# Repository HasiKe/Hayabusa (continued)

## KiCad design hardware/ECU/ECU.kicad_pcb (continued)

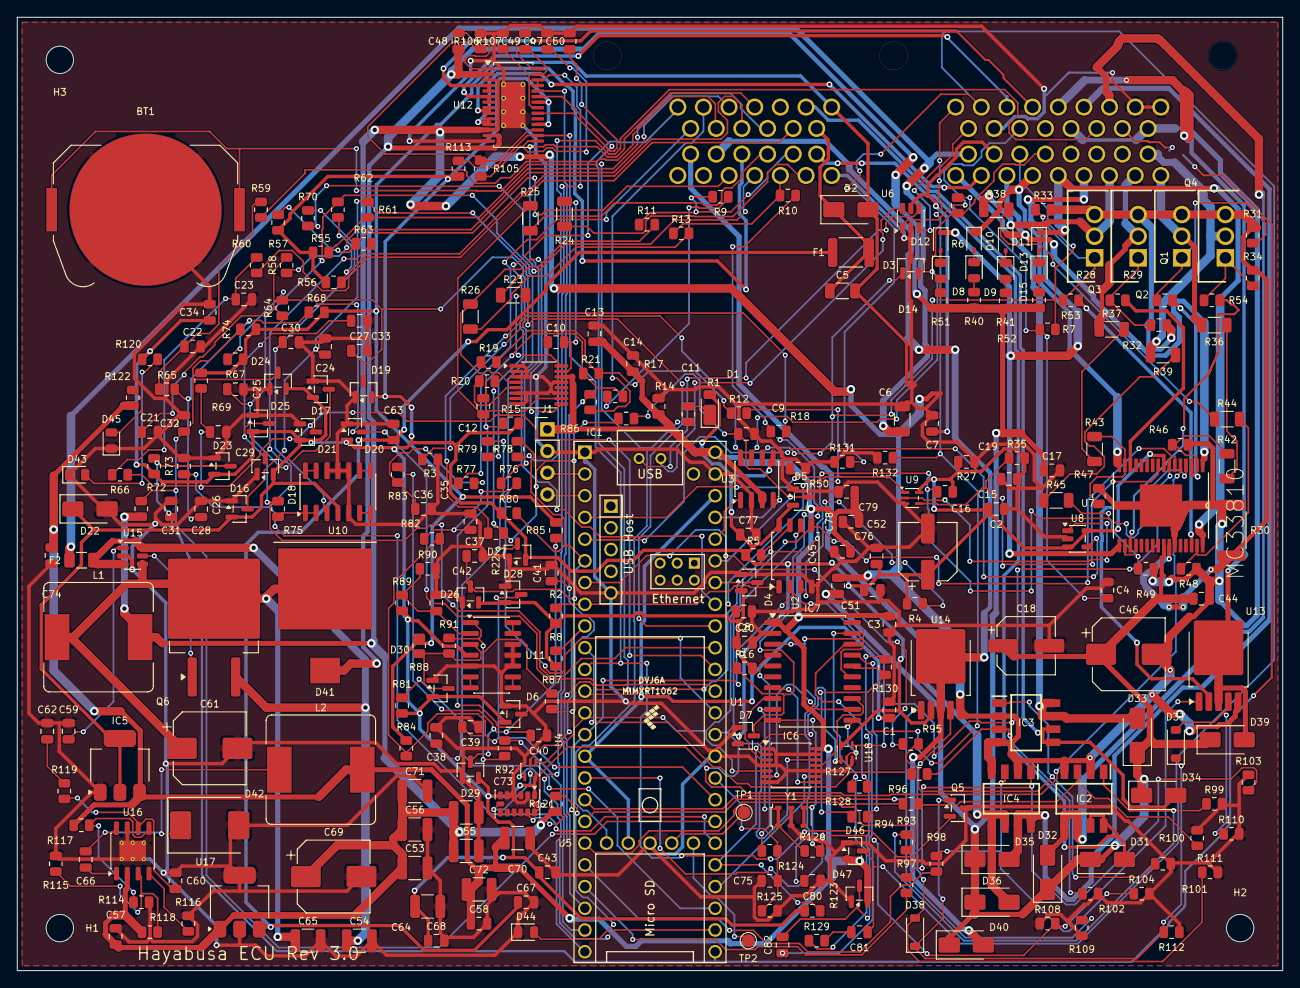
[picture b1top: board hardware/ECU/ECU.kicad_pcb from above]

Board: 2 copper layers, 148.0 x 111.5 mm, 307 parts (1 on the bottom side), 211 nets.

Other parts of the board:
H1, H2, H3: M3; MountingHole_3.2mm_M3

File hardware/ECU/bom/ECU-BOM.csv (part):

Reference,Qty,Value,Footprint,MPN,Manufacturer,DigiKey,DK_Stock,Mouser,MO_Stock,Chosen_Distributor,Datasheet,Validated,DNP,Notes
BT1,1,ML2032,BatteryHolder_Keystone_3034_1x20mm,3034,Keystone Electronics,36-3034-ND,,,,DigiKey,https://www.digikey.de/de/products/result?keywords=36-3034-ND,,,SMD-Halter 20 mm (Keystone 3034); Zelle ML2032 separat: Jauch ML2032 / DK 1908-ML2032-ND. Keine CR2032 (nicht ladbar)!
"C1,C38,C41,C43,C35,C42,C36,C37,C68,C74,C67,C21,C25,C22,C31,C32,C30,C34,C23,C24,C77,C7",22,100nF,0805,CC0805KRX7R9BB104,Yageo,311-1140-1-ND,,,,DigiKey,https://www.digikey.de/de/products/result?keywords=311-1140-1-ND,,,
C4,1,4.7nF,0805,CC0805KRX7R9BB472,Yageo,311-1133-1-ND,,,,DigiKey,https://www.digikey.de/de/products/result?keywords=311-1133-1-ND,,,
C5,1,10uF,1206,GRM31CR71E106KA12L,Murata,490-6518-1-ND,,,,DigiKey,https://www.digikey.de/de/products/result?keywords=490-6518-1-ND,,,
C6,1,100nF 100V,1206,C1206C104K1RACTU,KEMET,399-C1206C104K1RACTUCT-ND,,,,DigiKey,https://www.digikey.de/de/products/result?keywords=399-C1206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,,,
"C8,C9",2,470pF,0805,CC0805KRX7R9BB471,Yageo,311-1124-1-ND,,,,DigiKey,https://www.digikey.de/de/products/result?keywords=311-1124-1-ND,,,
"C11,C75",2,0.01uF,0805,CC0805KRX7R9BB103,Yageo,311-1136-1-ND,,,,DigiKey,https://www.digikey.de/de/products/result?keywords=311-1136-1-ND,,,
"C12,C10,C26",3,1nF,0805,C0805C102J5HACAUTO,Kemet,399-16591-1-ND,,,,DigiKey,https://www.digikey.de/de/products/result?keywords=399-16591-1-ND,,,
"C13,C3,C2,C15,C17",5,0.1uF,0805,CC0805KRX7R9BB104,Yageo,311-1140-1-ND,,,,DigiKey,https://www.digikey.de/de/products/result?keywords=311-1140-1-ND,,,
C14,1,1uF,0805,CC0805KKX7R7BB105,Yageo,311-1365-1-ND,,,,DigiKey,https://www.digikey.de/de/products/result?keywords=311-1365-1-ND,,,
"C18,C16",2,33uF,CP_Elec_6.3x7.7,EEE-1HA330XP,Panasonic,PCE3925CT-ND,,,,DigiKey,https://www.digikey.de/de/products/result?keywords=PCE3925CT-ND,,,
"C20,C19,C51,C52",4,100n,0805,CC0805KRX7R9BB104,Yageo,311-1140-1-ND,,,,DigiKey,https://www.digikey.de/de/products/result?keywords=311-1140-1-ND,,,
"C40,C39,C28,C29,C27,C33",6,10nF,0805,CC0805KRX7R9BB103,Yageo,311-1136-1-ND,,,,DigiKey,https://www.digikey.de/de/products/result?keywords=311-1136-1-ND,,,
"C45,C44",2,10n,0805,CC0805KRX7R9BB103,Yageo,311-1136-1-ND,,,,DigiKey,https://www.digikey.de/de/products/result?keywords=311-1136-1-ND,,,
C46,1,100u/50V,CP_Elec_8x10,EEE-FK1H101GP,Panasonic,PCE4323CT-ND,,,,DigiKey,https://www.digikey.de/de/products/result?keywords=PCE4323CT-ND,,,
C47,1,1u,0805,CC0805KKX7R7BB105,Yageo,311-1365-1-ND,,,,DigiKey,https://www.digikey.de/de/products/result?keywords=311-1365-1-ND,,,
C48,1,220n,0805,CC0805KKX7R9BB224,Yageo,311-1887-1-ND,,,,DigiKey,https://www.digikey.de/de/products/result?keywords=311-1887-1-ND,,,
C49,1,22n,0805,CC0805KRX7R9BB223,Yageo,311-1138-1-ND,,,,DigiKey,https://www.digikey.de/de/products/result?keywords=311-1138-1-ND,,,
C50,1,1n,0805,C0805C102J5HACAUTO,KEMET,399-16591-1-ND,,,,DigiKey,https://www.digikey.de/de/products/result?keywords=399-16591-1-ND,,,
"C53,C73,C54,C65",4,100nF/100V,1210,C1210C104K1RACTU,KEMET,399-C1210C104K1RACTUCT-ND,,,,DigiKey,https://www.digikey.de/de/products/result?keywords=399-C1210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,,,
"C56,C55",2,4.7uF/100V,1210,C3225X7S2A475K200AB,TDK,445-6042-1-ND,,,,DigiKey,https://www.digikey.de/de/products/result?keywords=445-6042-1-ND,,,
C57,1,1uF/50V,0805,CC0805KKX7R9BB105,Yageo,311-1886-1-ND,,,,DigiKey,https://www.digikey.de/de/products/result?keywords=311-1886-1-ND,,,
"C58,C63",2,10uF/10V,0805,CL21A106KPFNNNE,Samsung Electro-Mechanics,1276-1052-1-ND,,,,DigiKey,https://www.digikey.de/de/products/result?keywords=1276-1052-1-ND,,,
C60,1,39pF,0805,CC0805JRNPO9BN390,Yageo,311-1106-1-ND,,,,DigiKey,https://www.digikey.de/de/products/result?keywords=311-1106-1-ND,,,
"C61,C69",2,100uF/50V,CP_Elec_8x10,EEE-FK1H101GP,Panasonic,PCE4323CT-ND,,,,DigiKey,https://www.digikey.de/de/products/result?keywords=PCE4323CT-ND,,,
C62,1,6800pF,0805,CC0805KRX7R9BB682,Yageo,311-1135-1-ND,,,,DigiKey,https://www.digikey.de/de/products/result?keywords=311-1135-1-ND,,,
C64,1,22uF/10V,1210,GRM32ER71A226KE20L,Murata,490-1876-1-ND,,,,DigiKey,https://www.digikey.de/de/products/result?keywords=490-1876-1-ND,,,
"C66,C59",2,100nF/25V,0805,CC0805KRX7R9BB104,Yageo,311-1140-1-ND,,,,DigiKey,https://www.digikey.de/de/products/result?keywords=311-1140-1-ND,,,
C71,1,10uF/50V X7R,1210,C3225X7R1H106K250AC,TDK,445-C3225X7R1H106K250ACCT-ND,,,,DigiKey,https://www.digikey.de/de/products/result?keywords=445-C3225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,,,
"C72,C70",2,47uF/10V X7R,1210,CL32A476KOJNNNE,Samsung Electro-Mechanics,1276-3376-1-ND,,,,DigiKey,https://www.digikey.de/de/products/result?keywords=1276-3376-1-ND,,,
"C78,C80,C76",3,CC0805KRX7R9BB104,0805,CC0805KRX7R9BB104,Yageo,311-1140-1-ND,,603-CC805KRX7R9BB104,,DigiKey,https://www.yageo.com/upload/media/product/productsearch/dat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,,,
C79,1,CC0805KKX7R7BB475,0805,CC0805KKX7R7BB475,Yageo,311-1883-1-ND,,603-CC805KKX7R7BB475,,DigiKey,https://www.digikey.de/de/products/result?keywords=311-1883-1-ND,,,
"C82,C81",2,CC0805JRX7R9BB332,0805,CC0805JRX7R9BB332,Yageo,311-4277-1-ND,,,,DigiKey,https://yageogroup.com/content/datasheet/asset/file/UPY-GPHC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,,,
D1,1,D_Schottky,PowerDI-123,DFLS240-7,Diodes Incorporated,DFLS240-7DICT-ND,,,,DigiKey,https://www.digikey.de/de/products/result?keywords=DFLS240-7DICT-ND,,,
D2,1,SMAJ5.0A,SMA,SMAJ5.0A,Littelfuse,SMAJ5.0ALFCT-ND,,,,DigiKey,https://www.digikey.de/de/products/result?keywords=SMAJ5.0ALFCT-ND,,,
D3,1,NUP2105L,SOT-23,NUP2105LT1G,onsemi,NUP2105LT1GOSCT-ND,,,,DigiKey,https://www.digikey.de/de/products/result?keywords=NUP2105LT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,,,
"D11,D12,D10,D13",4,D,SOD-323,1N4448WX-TP,MCC,1N4448WXTPMSCT-ND,,,,DigiKey,https://www.digikey.de/de/products/result?keywords=1N4448WXT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,,,
"D15,D8,D14,D9",4,LED,0805,LTST-C170KRKT,Lite-On,160-1415-1-ND,,,,DigiKey,https://www.digikey.de/de/products/result?keywords=160-1415-1-ND,,,
D22,1,3V6 1W (SMA),SMA,1SMA5914BT3G,onsemi,1SMA5914BT3GOSCT-ND,,,,DigiKey,https://www.digikey.de/de/products/result?keywords=1SMA5914B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,,,
"D30,D27,D26,D28,D29,D7,D4,D5,D6,D20,D19,D25,D24,D23,D17,D16,D18,D21,D46,D47",20,BAV199,SOT-23,BAV199LT1G,onsemi,BAV199LT1GOSCT-ND,,,,DigiKey,https://www.digikey.de/de/products/result?keywords=BAV199LT1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,,,
"D31,D35,D40,D34,D36,D32,D33,D39",8,SS34,SMA,B340A-13-F,Diodes Incorporated,B340A-FDICT-ND,,,,DigiKey,https://www.digikey.de/de/products/result?keywords=B340A-FDICT-ND,,,Ersatz fuer SS34: 3A/40V Schottky in SMA (SS34 meist SMC)
"D38,D37",2,1N4148W,SOD-123,1N4148W-7-F,Diodes Incorporated,1N4148W-FDICT-ND,,,,DigiKey,https://www.digikey.de/de/products/result?keywords=1N4148W-FDICT-ND,,,
D41,1,SM8S24A,DO-218AB,SM8S24A,SMC Diode Solutions,1655-SM8S24ACT-ND,,,,DigiKey,https://www.digikey.de/de/products/result?keywords=1655-SM8S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,,,
D42,1,B560C,SMC,B560C-13-F,Diodes Incorporated,B560C-FDICT-ND,,,,DigiKey,https://www.digikey.de/de/products/result?keywords=B560C-FDICT-ND,,,
"D43,D44,D45",3,LED grn,0805,LTST-C170GKT,Lite-On,160-1179-1-ND,,,,DigiKey,https://www.digikey.de/de/products/result?keywords=160-1179-1-ND,,,
F1,1,150mA,1812,1812L014DR,Littelfuse,F3353CT-ND,,,,DigiKey,https://www.digikey.de/de/products/result?keywords=F3353CT-ND,,,"PTC 140mA hold (naechster Standardwert zu 150mA), 60V"
F2,1,3A / 63V,1206,0483003.DR,Littelfuse,18-0483003.DRCT-ND,,,,DigiKey,https://www.digikey.de/de/products/result?keywords=18-048300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,,,3A/65V flink 1206 (63V-Anforderung: 437er-Serie schafft nur 35V)
IC1,1,MAX9926UAEE_V+,QSOP-16_3.9x4.9mm_P0.635mm,MAX9926UAEE/V+,Analog Devices,MAX9926UAEE/V+-ND,,700-MAX9926UAEE/V+,,DigiKey,https://componentsearchengine.com/Datasheets/1/MAX9926UAEE_V+.pdf,,,
"IC3,IC4,IC2",3,ZXMS6006DT8,SOT153P700X170-8N,ZXMS6006DT8TA,Diodes Incorporated,ZXMS6006DT8TADICT-ND,,,,DigiKey,https://www.digikey.de/de/products/result?keywords=ZXMS6006D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,,,Last Time Buy 06.01.2027 - Bedarf sichern
IC5,1,LD1117S33,SOT-223-3_TabPin2,LD1117S33CTR,STMicroelectronics,497-1241-1-ND,,,,DigiKey,https://www.digikey.de/de/products/result?keywords=497-1241-1-ND,,,
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
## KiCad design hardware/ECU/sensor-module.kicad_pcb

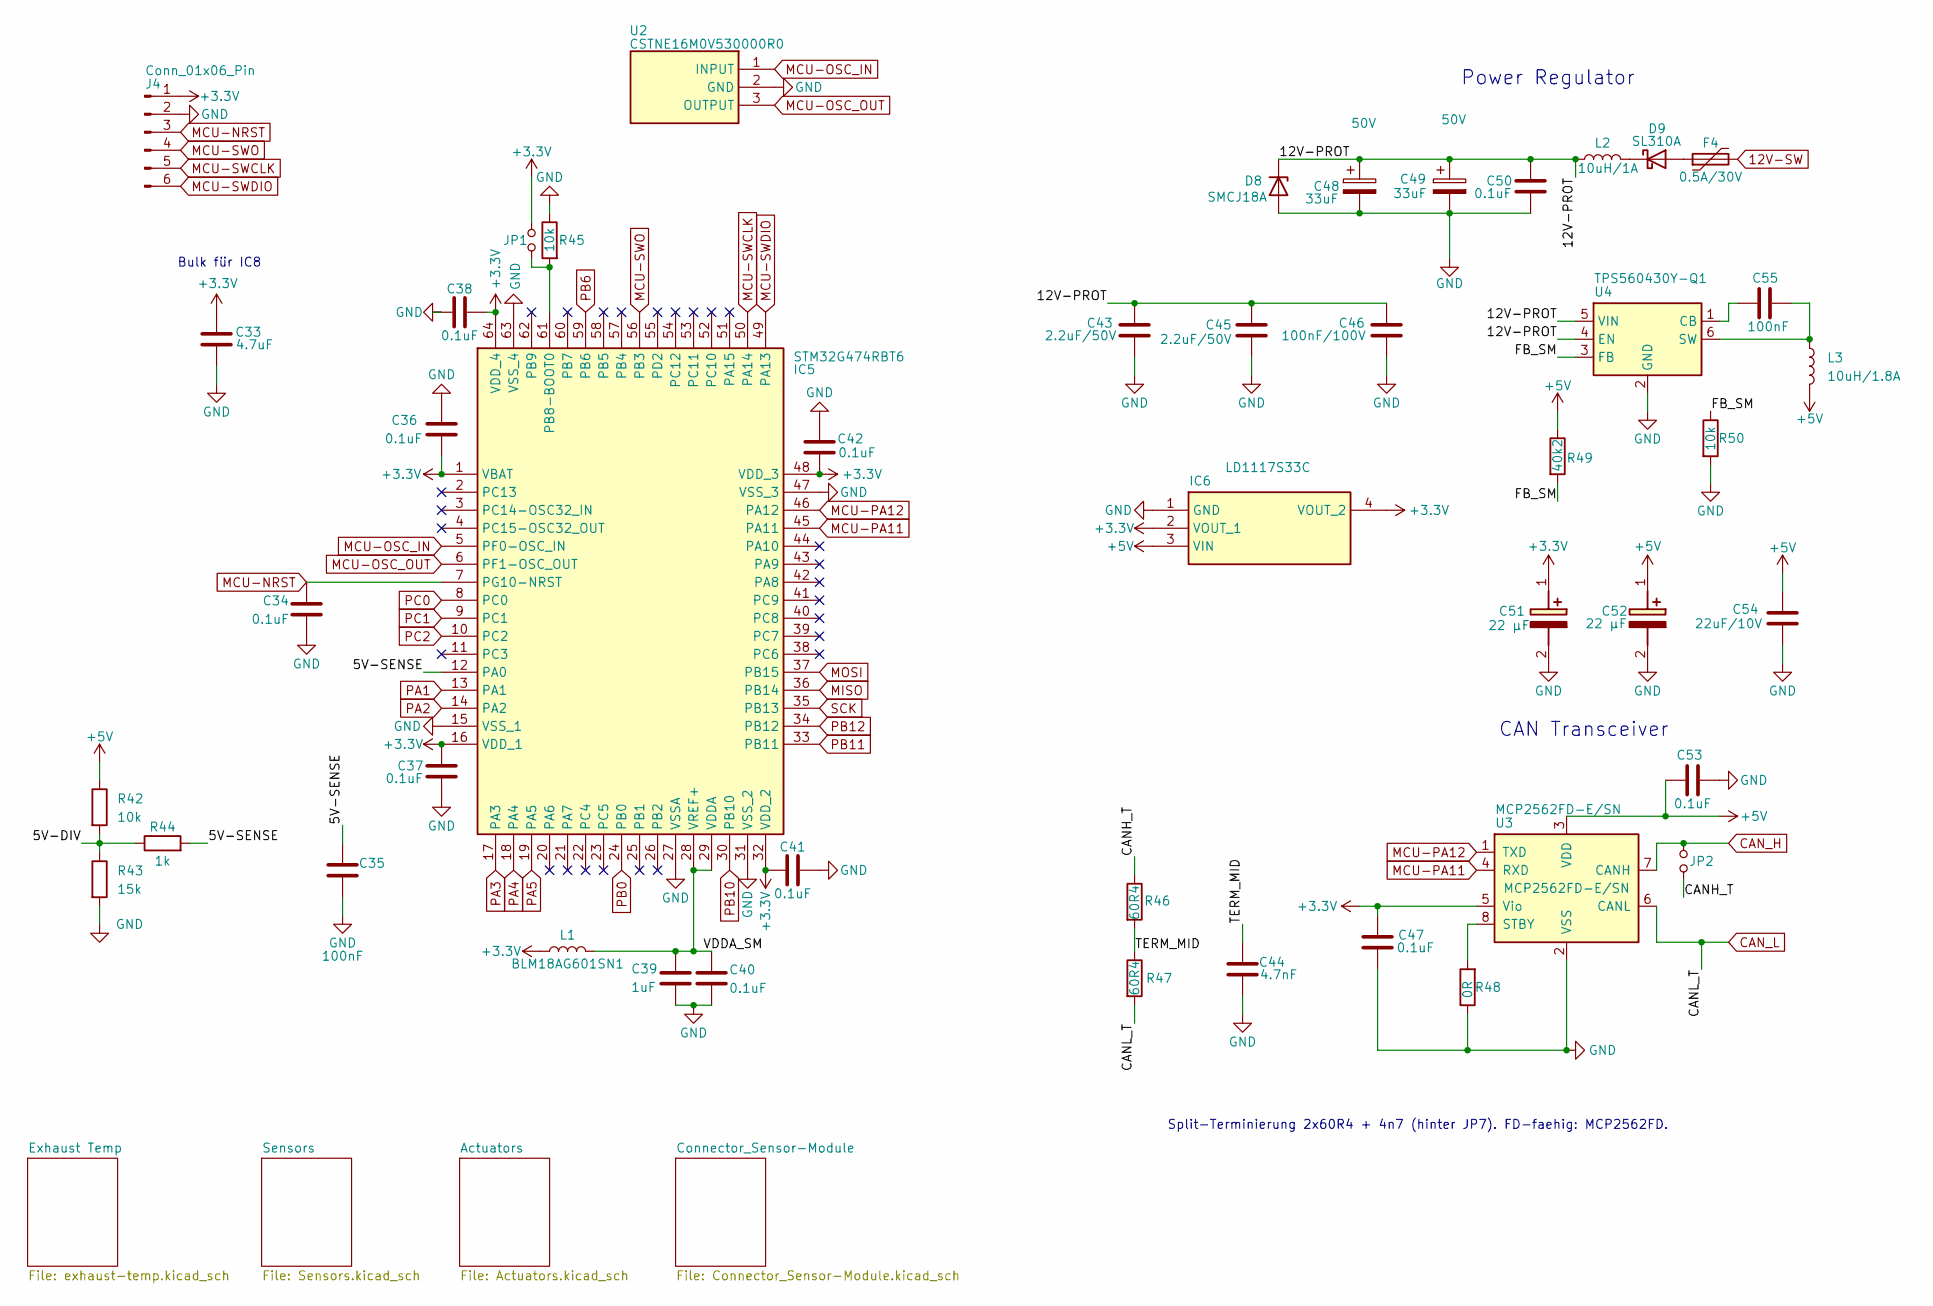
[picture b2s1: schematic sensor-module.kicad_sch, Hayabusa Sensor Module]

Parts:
C33: 4.7uF; C_0805_2012Metric; Manufacturer_Part_Number CC0805KKX7R7BB475; Digikey Part Number 311-1883-1-ND
C34, C36, C37, C38, C40, C41, C42, C47, C50, C53: 0.1uF; C_0805_2012Metric; Manufacturer_Part_Number CC0805KRX7R9BB104; Digikey Part Number 311-1140-1-ND
C35, C55: 100nF; C_0805_2012Metric; Manufacturer_Part_Number CC0805KRX7R9BB104; Digikey Part Number 311-1140-1-ND
C39: 1uF; C_0805_2012Metric; Manufacturer_Part_Number CC0805KKX7R7BB105; Digikey Part Number 311-1365-1-ND
C43, C45: 2.2uF/50V; C_1210_3225Metric; Manufacturer_Part_Number C3225X7R1H225K250AB; Digikey Part Number 445-1431-1-ND
C44: 4.7nF; C_0805_2012Metric; Manufacturer_Part_Number CC0805KRX7R9BB472; Digikey Part Number 311-1133-1-ND
C46: 100nF/100V; C_0805_2012Metric; Manufacturer_Part_Number C0805C104K1RACTU; Digikey Part Number 399-C0805C104K1RACTUCT-ND
C48, C49: 33uF; CP_Elec_6.3x7.7; Voltage 50V; Manufacturer_Part_Number EEE-1HA330XP; Digikey Part Number PCE3925CT-ND
C51, C52: 22 µF; EEE1AA221P; Manufacturer_Part_Number EEE-FK1H220P; Digikey Part Number PCE3811CT-ND
C54: 22uF/10V; C_1210_3225Metric; Manufacturer_Part_Number GRM32ER71A226KE20L; Digikey Part Number 490-1876-1-ND
D8: SMCJ18A; D_SMC; Manufacturer_Part_Number SMCJ18A; Digikey Part Number SMCJ18ALFCT-ND
D9: SL310A; D_SMA_Handsoldering; Manufacturer_Part_Number SL310A-TP; Digikey Part Number SL310A-TPMSCT-ND
F4: 0.5A/30V; Fuse_1812_4532Metric; Manufacturer_Part_Number 1812L050/60MR; Digikey Part Number F8132CT-ND
IC5: STM32G474RBT6; QFP50P1200X1200X160-64N; Manufacturer_Part_Number STM32G474RBT6; Mouser Part Number 511-STM32G474RBT6
IC6: LD1117S33C; Manufacturer_Part_Number LD1117S33CTR; Mouser Part Number N/A
J4: Conn_01x06_Pin; PinHeader_1x06_P2.54mm_Vertical; Manufacturer_Part_Number 61300611121; Digikey Part Number 732-5319-ND
JP1, JP2: Jumper_NO_Small; SolderJumper-2_P1.3mm_Open_Pad1.0x1.5mm
L1: BLM18AG601SN1; L_0603_1608Metric; Manufacturer_Part_Number BLM18AG601SN1D; Digikey Part Number 490-1014-1-ND
L2: 10uH/1A; L_1210_3225Metric; Manufacturer_Part_Number LQH32PN100MNCL; Digikey Part Number 490-LQH32PN100MNCLCT-ND
L3: 10uH/1.8A; L_Bourns_SRN6045TA; Part Nr SRN6045; Digikey Part Number SRN6045TA-100MCT-ND
R42, R50: 10k; R_0805_2012Metric; Manufacturer_Part_Number RC0805FR-0710KL; Digikey Part Number 311-10.0KCRCT-ND
R43: 15k; R_0805_2012Metric; Manufacturer_Part_Number RC0805FR-0715KL; Digikey Part Number 311-15.0KCRCT-ND
R44: 1k; R_0805_2012Metric; Manufacturer_Part_Number RC0805FR-071KL; Digikey Part Number 311-1.00KCRCT-ND
R45: 10k; R_0805_2012Metric; Manufacturer_Part_Number RC0805JR-0710KL; Digikey Part Number 311-10KARCT-ND
R46, R47: 60R4; R_0805_2012Metric; Manufacturer_Part_Number RC0805FR-0760R4L; Digikey Part Number 311-60.4CRCT-ND
R48: 0R; R_0805_2012Metric; Manufacturer_Part_Number RC0805JR-070RL; Digikey Part Number 311-0.0ARCT-ND
R49: 40k2; R_0805_2012Metric; Manufacturer_Part_Number RC0805FR-0740K2L; Digikey Part Number 311-40.2KCRCT-ND
U2: CSTNE16M0V530000R0; Manufacturer_Part_Number CSTNE16M0V530000R0; Mouser Part Number 81-CSTNE16M0V530000R
U3: MCP2562FD-E/SN; SOIC-8_3.9x4.9mm_P1.27mm; Manufacturer_Part_Number MCP2562FD-E/SN; Digikey Part Number MCP2562FD-E/SN-ND
U4: TPS560430Y-Q1; SOT-23-6; Manufacturer_Part_Number TPS560430YQDBVRQ1; Digikey Part Number 296-TPS560430YQDBVRQ1CT-ND

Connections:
12V-SW: F4.2; also elsewhere on the board
+3.3V: C33.1, C36.1, C37.1, C38.1, C41.1, C42.2, C47.1, C51.1 (+), IC5.1 (VBAT), IC5.16 (VDD_1), IC5.32 (VDD_2), IC5.48 (VDD_3), IC5.64 (VDD_4), IC6.2 (VOUT_1), IC6.4 (VOUT_2), J4.1, JP1.1, L1.1, U3.5 (Vio); also elsewhere on the board
+5V: C52.1 (+), C53.1, C54.1, IC6.3 (VIN), L3.2, R42.1, R49.1, U3.3 (VDD); also elsewhere on the board
/5V-DIV: R42.2, R43.1, R44.1
/5V-SENSE: C35.1, IC5.12 (PA0), R44.2
/12V-PROT: C43.1, C45.1, C46.1, C48.1, C49.1, C50.1, D8.1 (K), L2.1, U4.4 (EN), U4.5 (VIN)
/CANH_T: JP2.2, R46.1
/FB_SM: R49.2, R50.1, U4.3 (FB)
/TERM_MID: C44.1, R46.2, R47.1
/VDDA_SM: C39.1, C40.1, IC5.28 (VREF+), IC5.29 (VDDA), L1.2
ADC-Clamp-1: IC5.8 (PC0); also elsewhere on the board
ADC-Clamp-2: IC5.10 (PC2); also elsewhere on the board
ADC-Clamp-3: IC5.18 (PA4); also elsewhere on the board
ADC-Clamp-4: IC5.9 (PC1); also elsewhere on the board
ADC-Clamp-5: IC5.17 (PA3); also elsewhere on the board
ADC-Clamp-6: IC5.19 (PA5); also elsewhere on the board
ADC-Clamp-7: IC5.13 (PA1); also elsewhere on the board
ADC-Clamp-8: IC5.14 (PA2); also elsewhere on the board
CAN_H: JP2.1, U3.7 (CANH); also elsewhere on the board
CAN_L: R47.2, U3.6 (CANL); also elsewhere on the board
GND: C33.2, C34.2, C35.2, C36.2, C37.2, C38.2, C39.2, C40.2, C41.2, C42.1, C43.2, C44.2, C45.2, C46.2, C47.2, C48.2, C49.2, C50.2, C51.2 (-), C52.2 (-), C53.2, C54.2, D8.2 (A), IC5.15 (VSS_1), IC5.27 (VSSA), IC5.31 (VSS_2), IC5.47 (VSS_3), IC5.63 (VSS_4), IC6.1 (GND), J4.2, R43.2, R45.1, R48.1, R50.2, U2.2 (GND), U3.2 (VSS), U4.2 (GND); also elsewhere on the board
MCU-NRST: C34.1, IC5.7 (PG10-NRST), J4.3
MCU-OSC_IN: IC5.5 (PF0-OSC_IN), U2.1 (INPUT)
MCU-OSC_OUT: IC5.6 (PF1-OSC_OUT), U2.3 (OUTPUT)
MCU-PA11: IC5.45 (PA11), U3.4 (RXD)
MCU-PA12: IC5.46 (PA12), U3.1 (TXD)
MCU-SWCLK: IC5.50 (PA14), J4.5
MCU-SWDIO: IC5.49 (PA13), J4.6
MCU-SWO: IC5.56 (PB3), J4.4
MISO: IC5.36 (PB14); also elsewhere on the board
MOSI: IC5.37 (PB15)
unnamed: D9.2 (A), F4.1
unnamed: D9.1 (K), L2.2
unnamed: IC5.61 (PB8-BOOT0), JP1.2, R45.2
unnamed: R48.2, U3.8 (STBY)
unnamed: C55.1, U4.1 (CB)
unnamed: C55.2, L3.1, U4.6 (SW)
PB0: IC5.24 (PB0); also elsewhere on the board
PB6: IC5.59 (PB6); also elsewhere on the board
PB10: IC5.30 (PB10); also elsewhere on the board
PB11: IC5.33 (PB11); also elsewhere on the board
PB12: IC5.34 (PB12); also elsewhere on the board
SCK: IC5.35 (PB13); also elsewhere on the board

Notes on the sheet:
CAN Transceiver
Bulk für IC8
Split-Terminierung 2x60R4 + 4n7 (hinter JP7). FD-faehig: MCP2562FD.
Power Regulator

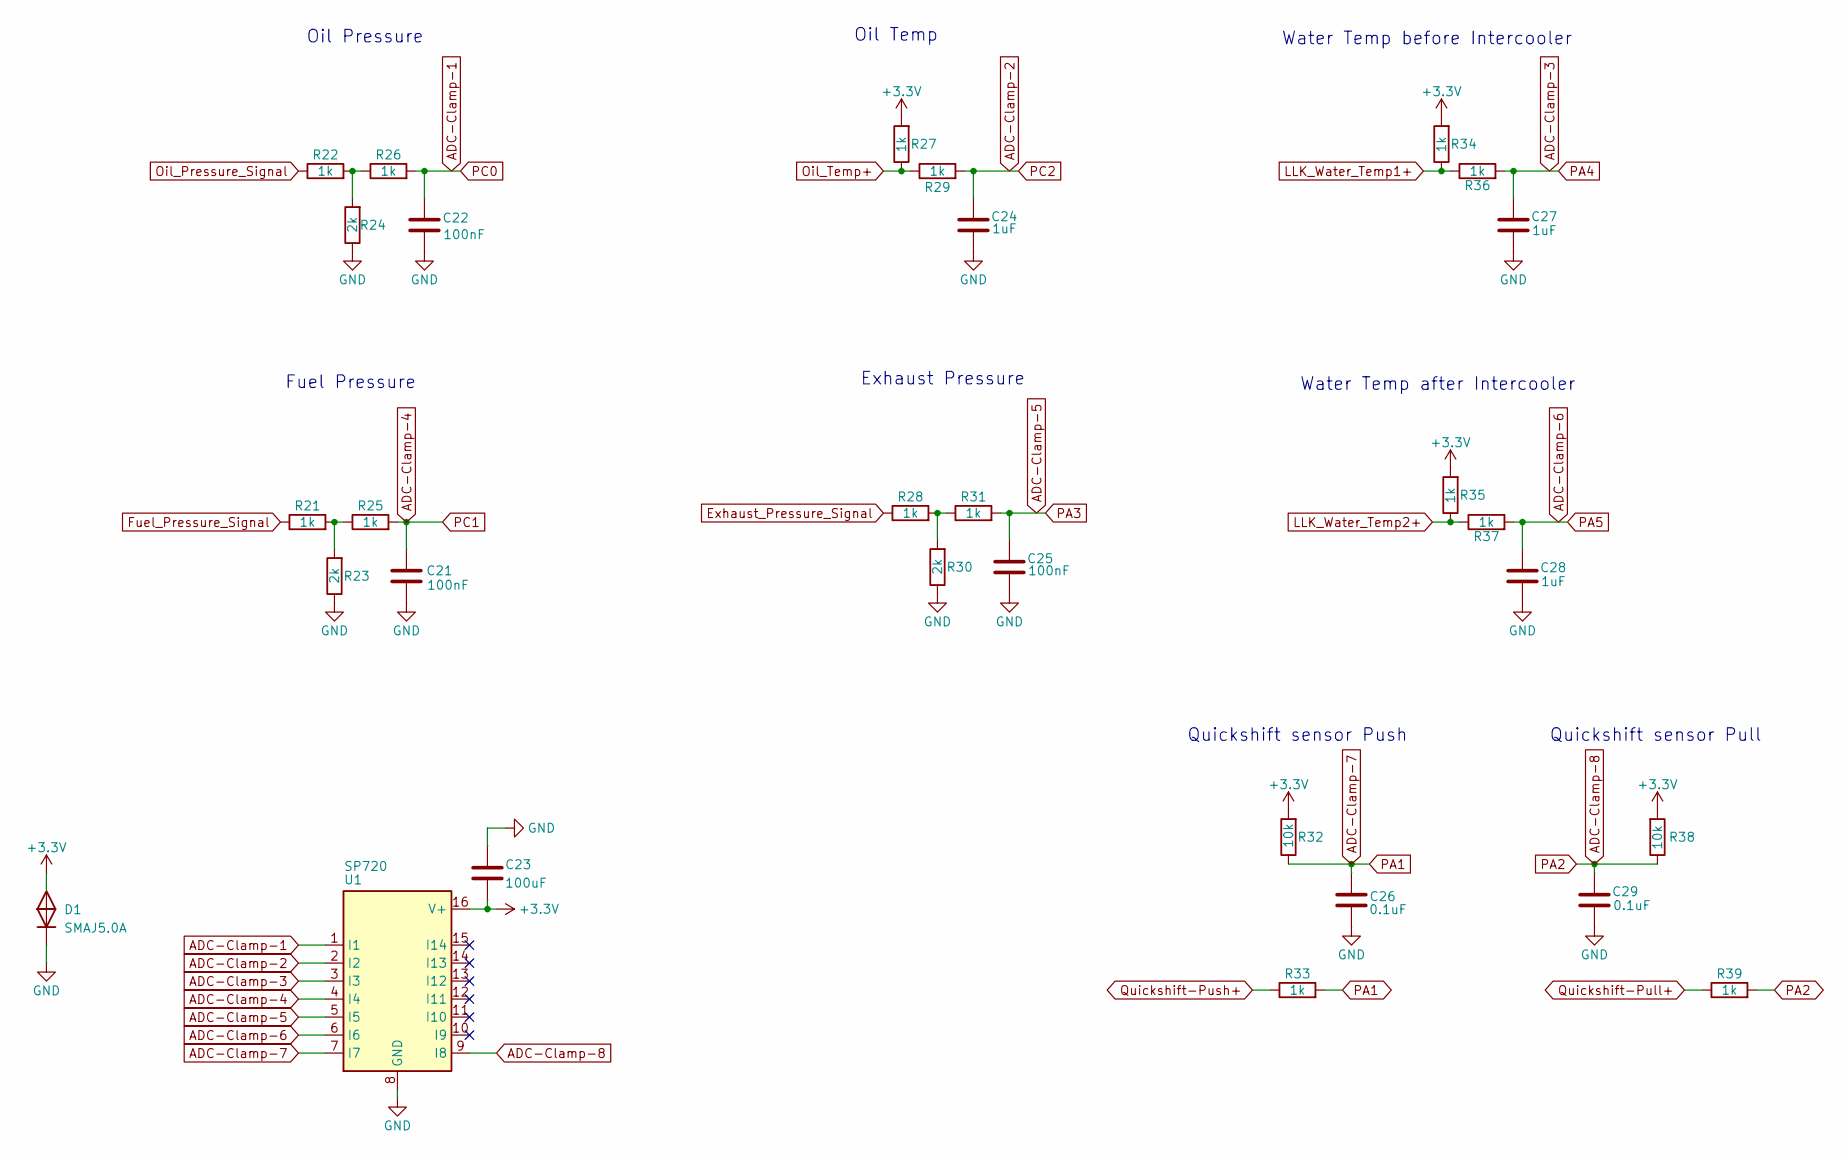
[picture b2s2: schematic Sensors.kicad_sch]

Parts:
C21, C22, C25: 100nF; C_0805_2012Metric; Manufacturer_Part_Number CC0805KRX7R9BB104; Digikey Part Number 311-1140-1-ND
C23: 100uF; C_1206_3216Metric; Manufacturer_Part_Number CL31A107MQHNNNE; Digikey Part Number 1276-1782-1-ND
C24, C27, C28: 1uF; C_0805_2012Metric; Manufacturer_Part_Number CC0805KKX7R7BB105; Digikey Part Number 311-1365-1-ND
C26, C29: 0.1uF; C_0805_2012Metric; Manufacturer_Part_Number CC0805KRX7R9BB104; Digikey Part Number 311-1140-1-ND
D1: SMAJ5.0A; D_SMA; Manufacturer_Part_Number SMAJ5.0A; Digikey Part Number SMAJ5.0ALFCT-ND
R21, R22, R25, R26, R27, R28, R29, R31, R33, R34, R35, R36, R37, R39: 1k; R_0805_2012Metric; Manufacturer_Part_Number RC0805FR-071KL; Digikey Part Number 311-1.00KCRCT-ND
R23, R24, R30: 2k; RESC2012X60N; Manufacturer_Part_Number RC0805FR-072KL; Mouser Part Number 603-RC0805FR-072KL
R32, R38: 10k; R_1206_3216Metric; Manufacturer_Part_Number RC1206FR-7W10KL; Digikey Part Number 13-RC1206FR-7W10KLTR-ND
U1: SP720; SOIC-16_3.9x9.9mm_P1.27mm; Manufacturer_Part_Number SP720ABTG; Digikey Part Number F3162CT-ND

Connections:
+3.3V: C23.2, D1.1, R27.2, R32.2, R34.2, R35.2, R38.2, U1.16 (V+); also elsewhere on the board
ADC-Clamp-1: C22.1, R26.2, U1.1 (I1); also elsewhere on the board
ADC-Clamp-2: C24.1, R29.2, U1.2 (I2); also elsewhere on the board
ADC-Clamp-3: C27.1, R36.2, U1.3 (I3); also elsewhere on the board
ADC-Clamp-4: C21.1, R25.2, U1.4 (I4); also elsewhere on the board
ADC-Clamp-5: C25.1, R31.2, U1.5 (I5); also elsewhere on the board
ADC-Clamp-6: C28.1, R37.2, U1.6 (I6); also elsewhere on the board
ADC-Clamp-7: C26.2, R32.1, R33.2, U1.7 (I7); also elsewhere on the board
ADC-Clamp-8: C29.2, R38.1, R39.2, U1.9 (I8); also elsewhere on the board
Exhaust_Pressure_Signal: R28.1; also elsewhere on the board
Fuel_Pressure_Signal: R21.1; also elsewhere on the board
GND: C21.2, C22.2, C23.1, C24.2, C25.2, C26.1, C27.2, C28.2, C29.1, D1.2, R23.1, R24.1, R30.1, U1.8 (GND); also elsewhere on the board
LLK_Water_Temp1+: R34.1, R36.1; also elsewhere on the board
LLK_Water_Temp2+: R35.1, R37.1; also elsewhere on the board
unnamed: R21.2, R23.2, R25.1
unnamed: R22.2, R24.2, R26.1
unnamed: R28.2, R30.2, R31.1
Oil_Pressure_Signal: R22.1; also elsewhere on the board
Oil_Temp+: R27.1, R29.1; also elsewhere on the board
Quickshift-Pull+: R39.1; also elsewhere on the board
Quickshift-Push+: R33.1; also elsewhere on the board

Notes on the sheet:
Oil Pressure
Quickshift sensor Pull
Water Temp after Intercooler
Oil Temp
Water Temp before Intercooler
Quickshift sensor Push
Fuel Pressure
Exhaust Pressure

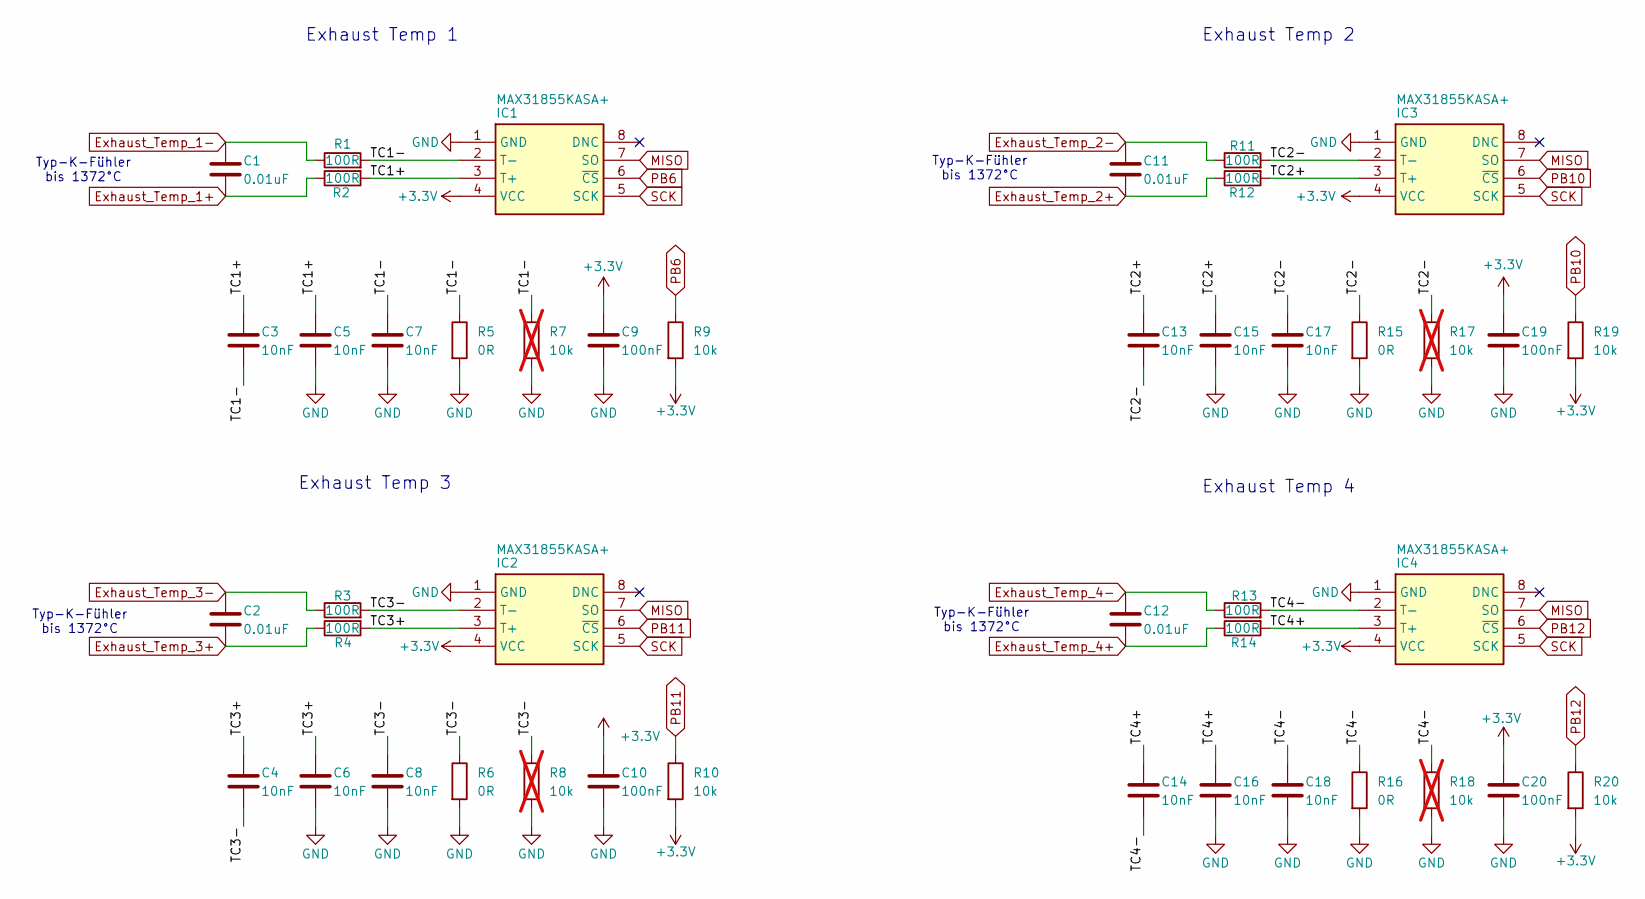
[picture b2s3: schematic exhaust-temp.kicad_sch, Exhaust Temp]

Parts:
C1, C2, C11, C12: 0.01uF; C_0805_2012Metric; Manufacturer_Part_Number CC0805KRX7R9BB103; Digikey Part Number 311-1136-1-ND
C3, C4, C5, C6, C7, C8, C13, C14, C15, C16, C17, C18: 10nF; C_0805_2012Metric; Manufacturer_Part_Number CC0805KRX7R9BB103; Digikey Part Number 311-1136-1-ND
C9, C10, C19, C20: 100nF; C_0805_2012Metric; Manufacturer_Part_Number CC0805KRX7R9BB104; Digikey Part Number 311-1140-1-ND
IC1, IC2, IC3, IC4: MAX31855KASA+; SOIC127P600X175-8N; Manufacturer_Part_Number MAX31855KASA+T; Mouser Part Number 700-MAX31855KASA+
R1, R2, R3, R4, R11, R12, R13, R14: 100R; ERJ6ENF1000V; Manufacturer_Part_Number ERJ-6ENF1000V; Digikey Part Number P100CCT-ND
R5, R6, R15, R16: 0R; R_0805_2012Metric; Manufacturer_Part_Number RC0805JR-070RL; Digikey Part Number 311-0.0ARCT-ND
R7, R8, R17, R18: 10k; R_0805_2012Metric; Manufacturer_Part_Number RC0805FR-0710KL; Digikey Part Number 311-10.0KCRCT-ND; not fitted
R9, R10, R19, R20: 10k; R_0805_2012Metric; Manufacturer_Part_Number RC0805FR-0710KL; Digikey Part Number 311-10.0KCRCT-ND

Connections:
+3.3V: C9.1, C10.1, C19.1, C20.1, IC1.4 (VCC), IC2.4 (VCC), IC3.4 (VCC), IC4.4 (VCC), R9.2, R10.2, R19.2, R20.2; also elsewhere on the board
/Exhaust Temp/TC1+: C3.1, C5.1, IC1.3 (T+), R2.2
/Exhaust Temp/TC1-: C3.2, C7.1, IC1.2 (T-), R1.2, R5.1, R7.1
/Exhaust Temp/TC2+: C13.1, C15.1, IC3.3 (T+), R12.2
/Exhaust Temp/TC2-: C13.2, C17.1, IC3.2 (T-), R11.2, R15.1, R17.1
/Exhaust Temp/TC3+: C4.1, C6.1, IC2.3 (T+), R4.2
/Exhaust Temp/TC3-: C4.2, C8.1, IC2.2 (T-), R3.2, R6.1, R8.1
/Exhaust Temp/TC4+: C14.1, C16.1, IC4.3 (T+), R14.2
/Exhaust Temp/TC4-: C14.2, C18.1, IC4.2 (T-), R13.2, R16.1, R18.1
Exhaust_Temp_1+: C1.2, R2.1; also elsewhere on the board
Exhaust_Temp_1-: C1.1, R1.1; also elsewhere on the board
Exhaust_Temp_2+: C11.2, R12.1; also elsewhere on the board
Exhaust_Temp_2-: C11.1, R11.1; also elsewhere on the board
Exhaust_Temp_3+: C2.2, R4.1; also elsewhere on the board
Exhaust_Temp_3-: C2.1, R3.1; also elsewhere on the board
Exhaust_Temp_4+: C12.2, R14.1; also elsewhere on the board
Exhaust_Temp_4-: C12.1, R13.1; also elsewhere on the board
GND: C5.2, C6.2, C7.2, C8.2, C9.2, C10.2, C15.2, C16.2, C17.2, C18.2, C19.2, C20.2, IC1.1 (GND), IC2.1 (GND), IC3.1 (GND), IC4.1 (GND), R5.2, R6.2, R7.2, R8.2, R15.2, R16.2, R17.2, R18.2; also elsewhere on the board
MISO: IC1.7 (SO), IC2.7 (SO), IC3.7 (SO), IC4.7 (SO); also elsewhere on the board
PB6: IC1.6 (~CS), R9.1; also elsewhere on the board
PB10: IC3.6 (~CS), R19.1; also elsewhere on the board
PB11: IC2.6 (~CS), R10.1; also elsewhere on the board
PB12: IC4.6 (~CS), R20.1; also elsewhere on the board
SCK: IC1.5 (SCK), IC2.5 (SCK), IC3.5 (SCK), IC4.5 (SCK); also elsewhere on the board

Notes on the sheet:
Typ-K-Fühler bis 1372°C
Exhaust Temp 1
Exhaust Temp 4
Exhaust Temp 2
Typ-K-Fühler bis 1372°C
Exhaust Temp 3

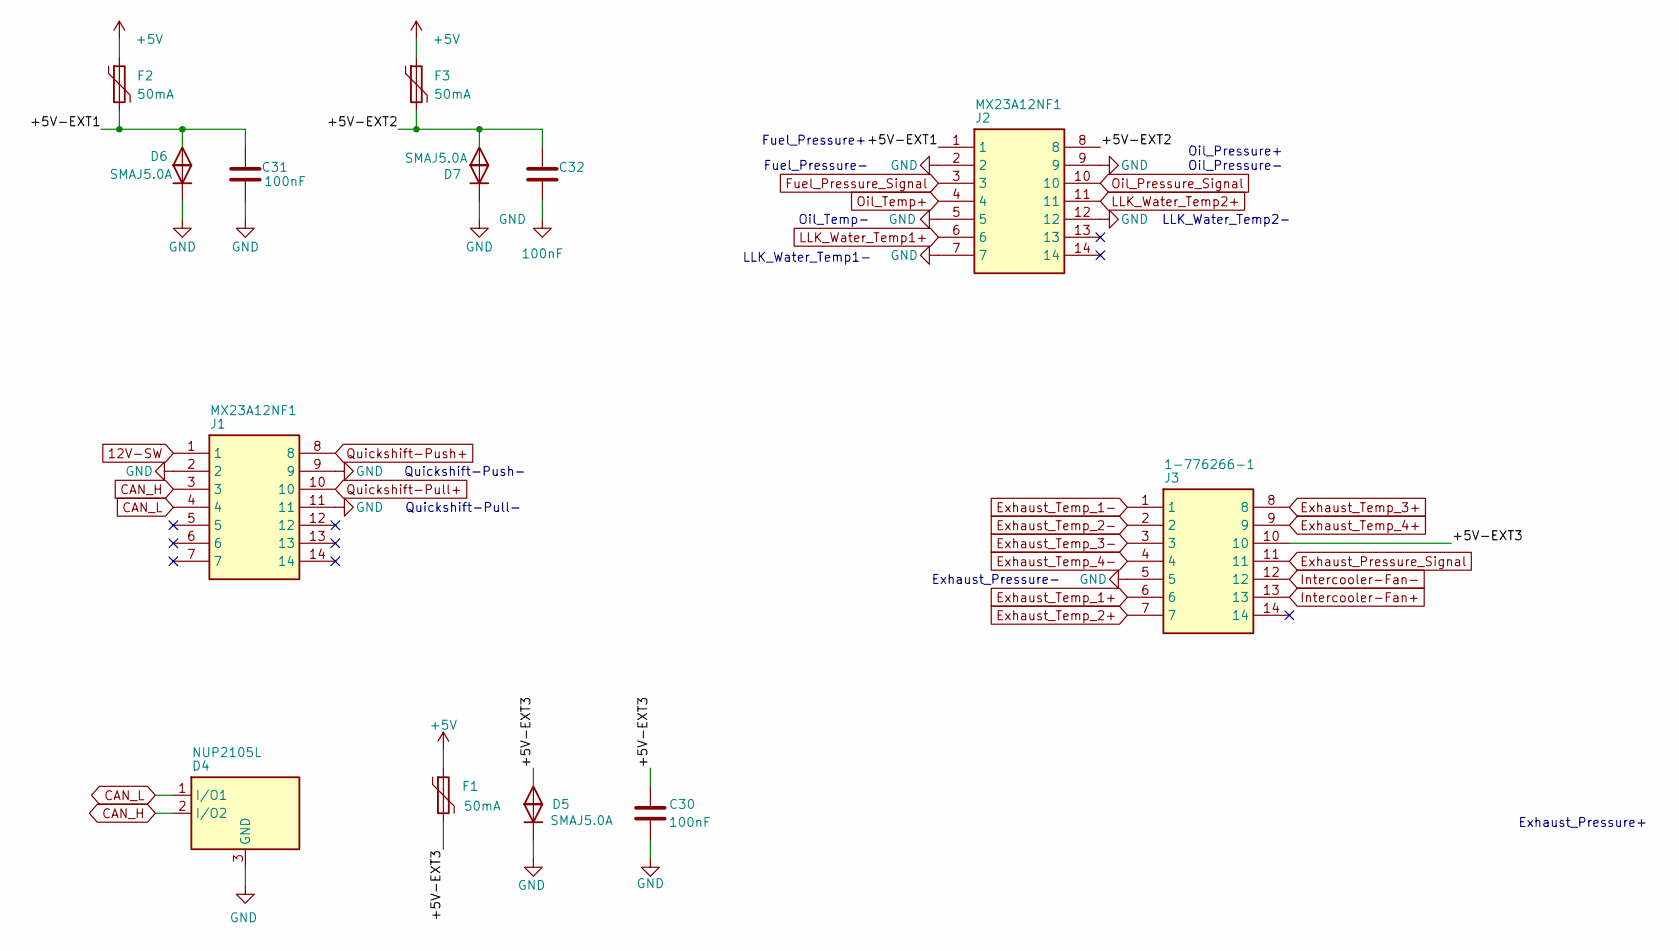
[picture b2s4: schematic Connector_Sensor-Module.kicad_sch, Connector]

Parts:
C30, C31, C32: 100nF; C_0805_2012Metric; Manufacturer_Part_Number CC0805KRX7R9BB104; Digikey Part Number 311-1140-1-ND
D4: NUP2105L; SOT-23; Manufacturer_Part_Number NUP2105LT1G; Digikey Part Number NUP2105LT1GOSCT-ND
D5, D6, D7: SMAJ5.0A; D_SMA; Manufacturer_Part_Number SMAJ5.0A; Digikey Part Number SMAJ5.0ALFCT-ND
F1, F2, F3: 50mA; Fuse_1206_3216Metric; Manufacturer_Part_Number 0ZCJ0005FF2E; Digikey Part Number 5923-0ZCJ0005FF2ECT-ND
J1, J2: MX23A12NF1; Mouser Part Number 656-MX23A12NF1
J3: 1-776266-1; 17762661; Manufacturer_Part_Number 1-776266-1; Mouser Part Number 571-1-776266-1

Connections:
12V-SW: J1.1, J3.13; also elsewhere on the board
+5V: F1.1, F2.1, F3.1; also elsewhere on the board
/Connector_Sensor-Module/+5V-EXT1: C31.1, D6.1, F2.2, J2.1
/Connector_Sensor-Module/+5V-EXT2: C32.1, D7.1, F3.2, J2.8
/Connector_Sensor-Module/+5V-EXT3: C30.1, D5.1, F1.2, J3.10
CAN_H: D4.2 (I/O2), J1.3; also elsewhere on the board
CAN_L: D4.1 (I/O1), J1.4; also elsewhere on the board
Exhaust_Pressure_Signal: J3.11; also elsewhere on the board
Exhaust_Temp_1+: J3.6; also elsewhere on the board
Exhaust_Temp_1-: J3.1; also elsewhere on the board
Exhaust_Temp_2+: J3.7; also elsewhere on the board
Exhaust_Temp_2-: J3.2; also elsewhere on the board
Exhaust_Temp_3+: J3.8; also elsewhere on the board
Exhaust_Temp_3-: J3.3; also elsewhere on the board
Exhaust_Temp_4+: J3.9; also elsewhere on the board
Exhaust_Temp_4-: J3.4; also elsewhere on the board
Fuel_Pressure_Signal: J2.3; also elsewhere on the board
GND: C30.2, C31.2, C32.2, D4.3 (GND), D5.2, D6.2, D7.2, J1.2, J1.9, J1.11, J2.2, J2.5, J2.7, J2.9, J2.12, J3.5; also elsewhere on the board
Intercooler-Fan-: J3.12; also elsewhere on the board
LLK_Water_Temp1+: J2.6; also elsewhere on the board
LLK_Water_Temp2+: J2.11; also elsewhere on the board
Oil_Pressure_Signal: J2.10; also elsewhere on the board
Oil_Temp+: J2.4; also elsewhere on the board
Quickshift-Pull+: J1.10; also elsewhere on the board
Quickshift-Push+: J1.8; also elsewhere on the board

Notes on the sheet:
Fuel_Pressure+
Exhaust_Pressure-
LLK_Water_Temp2-
Exhaust_Pressure+
Quickshift-Pull-
Oil_Temp-
Oil_Pressure+
Fuel_Pressure-
LLK_Water_Temp1-
Oil_Pressure-
Quickshift-Push-

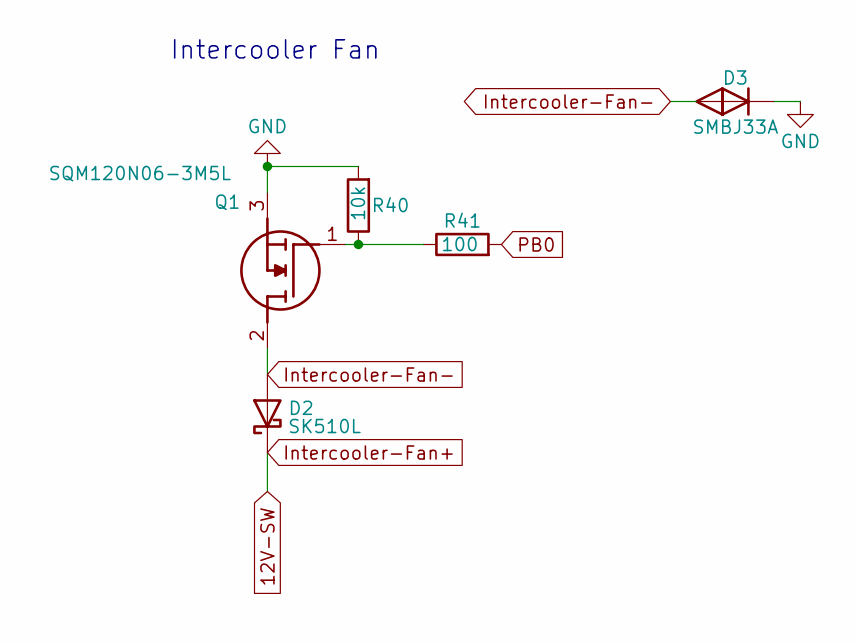
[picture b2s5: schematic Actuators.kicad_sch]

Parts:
D2: SK510L; D_SMC; Manufacturer_Part_Number SK510L-TP; Digikey Part Number SK510L-TPMSCT-ND
D3: SMBJ33A; D_SMB; Manufacturer_Part_Number SMBJ33A; Digikey Part Number SMBJ33ALFCT-ND
Q1: SQM120N06-3M5L; TO-263-2; Manufacturer_Part_Number SQM120N06-3M5L_GE3; Mouser Part Number 942-IRLB8721PBF
R40: 10k; R_1206_3216Metric; Manufacturer_Part_Number RC1206FR-7W10KL; Digikey Part Number 13-RC1206FR-7W10KLTR-ND
R41: 100; ERJ6ENF1000V; Manufacturer_Part_Number ERJ-6ENF1000V; Digikey Part Number P100CCT-ND

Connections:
12V-SW: D2.1 (K); also elsewhere on the board
GND: D3.2, Q1.3 (S), R40.2; also elsewhere on the board
Intercooler-Fan-: D2.2 (A), D3.1, Q1.2 (D); also elsewhere on the board
unnamed: Q1.1 (G), R40.1, R41.1
PB0: R41.2; also elsewhere on the board

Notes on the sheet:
Intercooler Fan
